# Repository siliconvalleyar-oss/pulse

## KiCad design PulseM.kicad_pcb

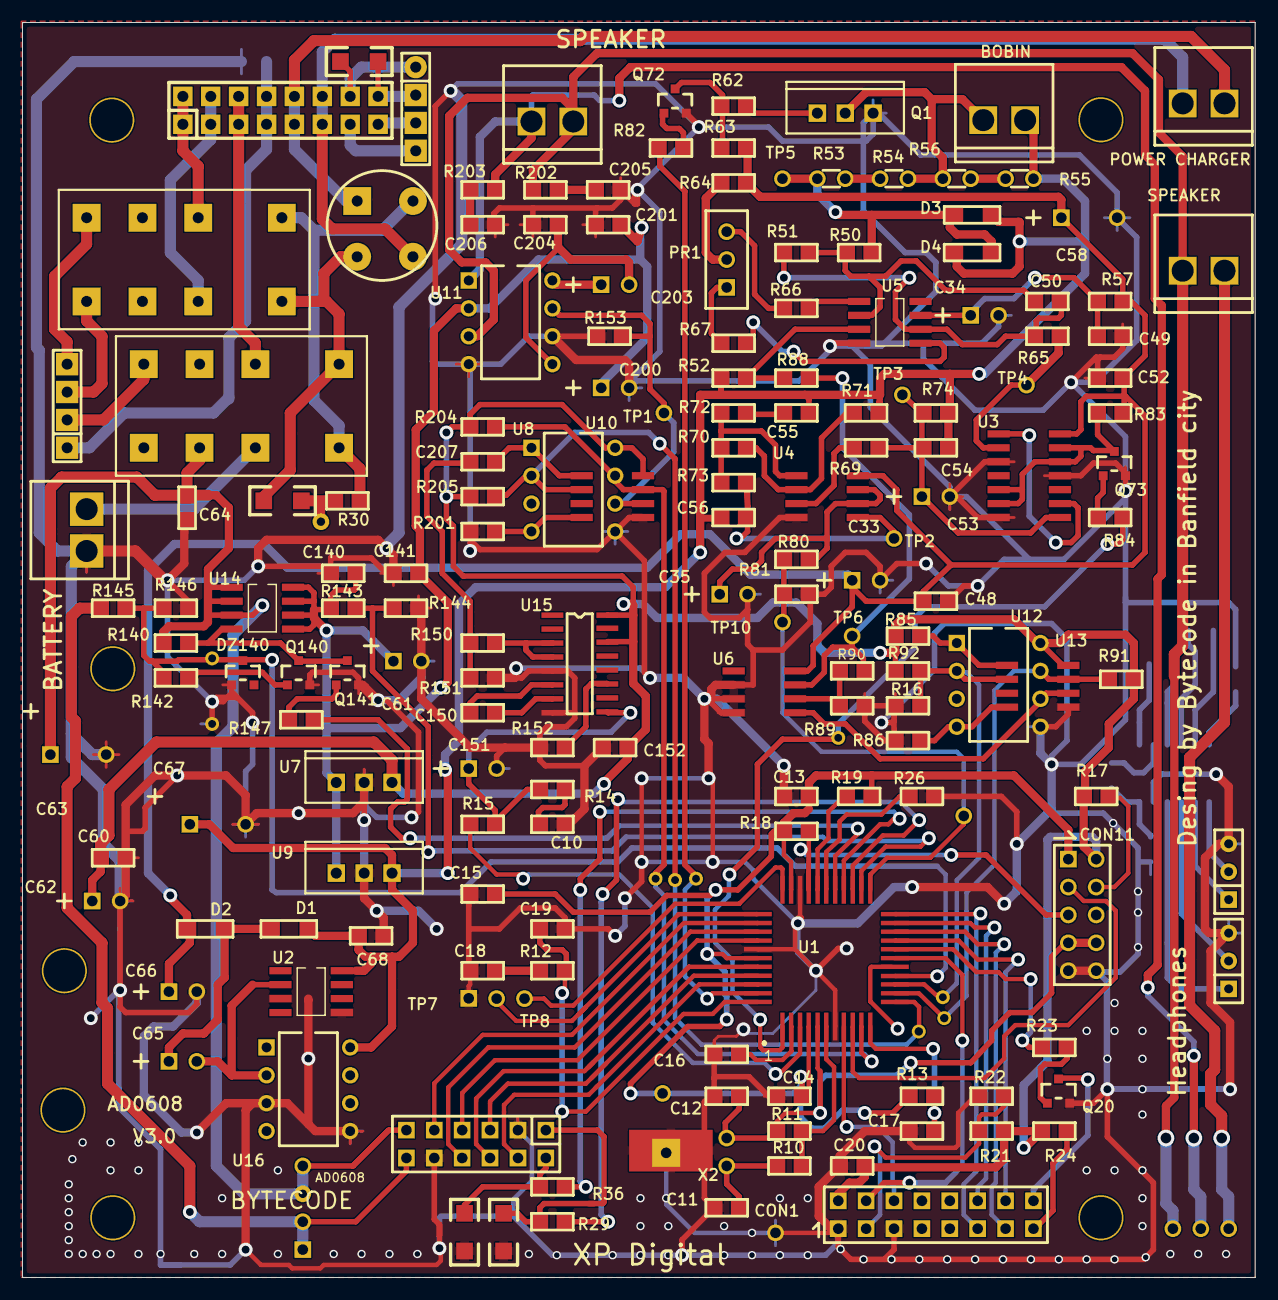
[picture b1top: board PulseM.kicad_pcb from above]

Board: 2 copper layers, 112.3 x 114.3 mm, 205 parts (0 on the bottom side), 136 nets.

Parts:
4Cell: SIP4
BALANCER: IDC16
BATTERY: NEWBOR
BOBIN: NEWBOR
BRIDGE: BRIDGE
Button: CON12SIL
C10, C13, C14, C15, C16, C17, C20, C48, C49, C60#2, C64#2, C68, C141, C152, C201, C204, C205, C206: 100nF; 0805
C11, C12: 27pF; 0805
C18: 470nF; 0805
C19: 22nF; 0805
C33, C61#2, C62#2, C65, C151, C200, C203: 10uF/16V; CAP100RP
C34: 100uF/25V; CAP100RP
C35: 1uF/25V; CAP100RP
C50, C207: 470pF; 0805
C52, C54, C55, C56: 100n; 0805
C53: 1uF/16V; CAP100RP
C58: 1000uF/25V; CAP200RP
C60, C61, C62, C63#2, C64: 0805
C63, C67: 1000uF/25V; CAP200RP2
C66: 47uF/25V; CAP100RP
C140: 1uF; 0805
C150: 10nF; 0805
CON1: DISPLAY LCD; CON16F2
CON11: CON10FF
D1, D2, D3, D4: 1N4148; 1206K
DZ140: 4V7; SOT-23(A1A2K)
FP1, FP2, FP4, FP5, FP6, FP7, FP8, FP9, FP10, FP11, FP12, FP16, FP17, FP18, FP20, FP22, FP23, FP24, FP27, FP28, FP105, FP105#2, FP105#3, FP105#4, FP105#5, FP105#6, FP105#7: FreePad
LED CHARGER: SIP4
Led1, Led2, Led3, Led4: 1206
NR1, NR2, NR3: CAP200RP2
PO1, PO2: SIP3
POWER CHARGER: NEWBOR
PR1: 200K - MULTIVUELTAS; PR3
Q1: TO220
Q20: SOT-23(BEC)
Q72, Q73, Q140, Q141: BC846; SOT-23(BEC)
R10: 330K; 0805
R11, R51: 10M; 0805
R12: 2K2; 0805
R13, R17, R18, R19, R21, R23, R26, R63, R66, R67, R69, R74, R80, R82, R83, R84, R85, R86, R89, R91, R92, R142, R143, R147: 10K; 0805
R14, R201: 0; 0805
R15, R70, R146: 47K; 0805
R16, R64, R72, R73, R88: 100K; 0805
R22, R29, R30, R31, R36, R65, R144: 1K; 0805
R24: 10; 0805
R50, R52, R57: 100; 0805
R53, R55: 390; RES100
R54, R56: 100; RES100
R62: 56; 0805
R71: 330; 0805
R81, R145, R153: 4K7; 0805
R90: 33K; 0805
R140: 100k; 0805
R150: 390k; 0805
R151: 470; 0805
R152: 150k; 0805
R202, R203: 10R; 0805
R204, R205: 10k; 0805
RL1, RL2: RELE
SPEAKER: NEWBOR
SPEAKER#2: NEWBOR
TP1: AUDIO; TP
TP2: AMP2; TP
TP3: SAMP; TP
TP4: AMP1; TP
TP5: PULSE; TP
TP6: AJUSTE; TP
TP7: BT7; TP
TP8: BT8; TP
TP10: ADC; TP
U1: MC68HC908AP32QFP44; QFP44
U2, U4, U5, U6, U10, U13: SO8
U3: SO14
U7: TO220
U8, U12: DIP-8
U9: 7809; TO220
U11, U16: DIP8
U14: IRF7204; SO8
U15: NSOIC16
U50: SO16
X2: 32768Hz; CRYSTAL100

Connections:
5VCC: C13.2, C14.2, C15.2, CON11.1, FP23.23, R13.2, R18.2, R19.1, U1.4, U1.32, U1.39
9V: BOBIN.2, C54.1, C55.1, C56.1, C67.1, C68.1, D1.1, D3.1, D4.2, R52.1, R55.1, R71.1, R74.1, U2.8, U9.3, U16.8
16V: C33.1, C48.1, C52.1, C58.1, C66.1, D2.2, R57.1, R63.1, R64.1, R83.2, U3.14, U4.8, U6.8
+5: C60.2, C64.2, U50.16
+5V: C20.2, C60#2.1, C62#2.1, C152.1, CON1.2, CON11.2, R17.2, R21.1, R24.1, R85.1, R91.2, R92.2, R204.2, R205.2, U7.3, U8.8, U10.8, U12.8, U13.8, U15.14, U15.16
+12V: C61#2.1, C140.2, C141.2, C200.1, C201.2, R143.2, U7.1, U9.1, U11.2, U14.5, U14.6, U14.7, U14.8
ADCMET1: C56.2, R73.1, TP2.1, U4.5
ADCMETAL: FP22.22, R80.2, R81.1, TP10.1, U1.23
ADCMETALHV: C35.1, R80.1, U4.6, U4.7
AJUSTE: R88.1, R90.2, TP6.1, U6.7
AJUSTE5V: U6.5, U12.6, U13.6
AJUSTEINTER: C207.1, U8.1, U10.1
AJUSTENEG: R201.2, U8.4, U10.4
AMP1: R65.2, TP4.1, U3.2
AONIVE: R70.1, R71.2, U4.2
AOOUT: R70.2, R72.2, R73.2, U4.1
AUDIOATENU: R153.1, TP1.1, U8.6, U10.6, U11.7
AUDIO_IN: C151.1, R14.1, R15.1, U15.9
AUDIO_OUT: C207.2, R150.1, R151.1
BACKA: CON1.15, R24.2
BACKBA: Q20.1, R23.1
BACKC: CON1.16, Q20.2
BACKLIGHT: R23.2, U1.18
BOTON1: Button.4, U1.42
BOTON2: Button.5, U1.41
BOTON3: Button.6, U1.40
BOTON4: Button.7, U1.37
BOTON5: Button.8, U1.36
BOTON6: Button.9, U1.35
BOTON7: TP7.1, U1.34
BOTON8: TP8.1, U1.33
C1NET00004: C150.1, U15.6
C1NET00010: C150.2, U15.7
CEL1: 4Cell.1, BALANCER.7, BALANCER.8, R31.1
CEL2: BALANCER.5, BALANCER.6, RL1.2
CEL3: BALANCER.3, BALANCER.4, RL2.7
CHARGE-: FP12.12, SPEAKER.2
CONTLCD: CON1.3, R21.2, R22.1
ENCENDIDO: Q140.2, Q141.2, R140.2, U14.4
ENTREERES: R53.1, R54.2
FILTROIN: C55.2, R72.1
FLITMIC: C18.1, R12.1
GNDA: BATTERY.1, Button.3, Button.10, C10.1, C11.2, C12.2, C13.1, C14.1, C15.1, C16.1, C17.2, C18.2, C19.2, C20.1, C33.2, C34.2, C35.2, C48.2, C49.2, C52.2, C53.2, C58.2, C60#2.2, C61#2.2, C62#2.2, C63.2, C63#2.2, C64.1, C64#2.2, C66.2, C67.2, C68.2, C140.1, C141.1, C151.2, C152.2, C200.2, C201.1, C204.1, C205.1, C206.1, CON1.1, CON1.5, CON11.9, CON11.10, DZ140.1, FP1.1, FP17.17, FP27.27, Led1.2, Led2.2, NR1.1, NR3.1, PO1.3, PO2.3, Q1.3, Q20.3, Q72.3, Q73.3, Q140.3, Q141.3, R16.1, R22.2, R26.1, R31.2, R81.2, R86.2, R89.1, R144.1, R146.1, R151.2, R152.1, R153.2, R201.1, U1.7, U1.31, U1.38, U2.3, U2.5, U3.3, U3.7, U3.11, U4.4, U5.4, U6.2, U6.3, U6.4, U7.2, U8.5, U9.2, U10.5, U11.4, U11.6, U12.5, U13.5, U15.5, U15.8, U16.3, U16.5, U50.15
INAUDFIOD: C203.2, C204.2, U11.5
IRQ: CON11.4, R17.1
IRQINT: CON11.3, U1.9
KEWPWRBASE: Q140.1, R142.1
KEY_SENSE: DZ140.3, FP16.16, R142.2, R145.2, R146.2, U1.15
LCDDATA1: CON1.11, U1.22
LCDDATA2: CON1.12, U1.21
LCDDATA3: CON1.13, U1.20
LCDDATA4: CON1.14, U1.19
LCDE: CON1.6, U1.8
LCDRS: CON1.4, U1.17
LED1: R29.1, U1.25
LED2: R36.1, U1.26
LLAVEDISP: Q73.2, R83.1, U3.5, U3.6, U3.12, U3.13
LLAVEINTER: U3.1, U3.9
LLAVEPOUT: C53.1, C54.2, R69.1, R74.2, TP3.1, U3.8
LMSALIDA1: C50.2, R51.2, R65.1, U5.6
MEDIR_VCC: R143.1, R144.2, U1.24
N4V7: FP4.4, Led3.2, R30.2
NET00000: R66.2, U5.1
NET00001: R67.2, U5.5
NET00002: Button.1, Led1.1, R29.2
NET00003: Button.2, Led2.1, R36.2
NET00008: C205.2, R202.1
NET00011: C206.2, R203.1
NET00012: C203.1, U11.8
NET00022: C34.1, C49.1, R57.2, U5.7
NET00035: C10.2, R14.2
NET00046: R26.2, U1.28
NET00052: R19.2, U1.29
NET00069: R89.2, R90.1, U6.6
NET00070: R85.2, U12.1, U13.1
NET00071: R86.1, U12.4, U13.4
NET00102: C65.1, D1.2, D2.1
NET00103: C65.2, U2.2, U16.2
NET00107: R52.2, R88.2, U5.3
NET00110: BOBIN.1, Q1.2, R54.1, R56.2
NET00111: R55.2, R56.1
NET00112: Q1.1, R62.1
NET00113: Q72.2, R62.2, R63.2
NET00114: Q72.1, R82.1
NET00115: PR1.1, R67.1
NET00116: PR1.3, R66.1
NET00117: PR1.2, R64.2
NET00124: Q73.1, R84.1
NET00128: R69.2, U4.3
NET00132: R10.2, R11.1, U1.6
NET00134: C19.1, R12.2, U1.44
NET00144: C11.1, R10.1, X2.1
NET00160: C16.2, U1.2
NetC61_1: C61.1, U50.1
NetC61_2: C61.2, U50.3
NetC62_1: C62.1, U50.4
NetC62_2: C62.2, U50.5
NetC63_1: C63#2.1, U50.6
NetLED_1: BALANCER.14, LED CHARGER.1, Led4.1
NetLED_2: BALANCER.16, LED CHARGER.2, Led4.2
NetLED_3: BALANCER.15, LED CHARGER.3
NetLED_4: BALANCER.13, LED CHARGER.4
NetRL1_4: 4Cell.2, RL1.4
NetRL1_5: BATTERY.2, RL1.7
NetRL2_4: 4Cell.4, RL2.4
NetRL2_5: 4Cell.3, RL2.5
NetU50_2: C60.1, U50.2
NetU50_11: PO1.2, U50.11
NetU50_12: PO1.1, U50.12
NetU50_13: PO2.2, U50.13
NetU50_14: PO2.1, U50.14
OPEINTE: C50.1, R50.2, R51.1, U5.2
OSC1: C12.1, CON11.7, CON11.8, R11.2, U1.5, X2.2
PORTA0: CON11.5, R18.1, U1.30
PULSEAMPL: D3.2, D4.1, R50.1, R53.2, TP5.1
PULSO: FP7.7, R82.2, U1.43
PWR1: Button.11, C63.1, C64#2.1, FP2.2, FP18.18, R140.1, RL1.6, U14.1, U14.2, U14.3
PWR2: Button.12, FP20.20, NR2.1, R145.1
RESETM: C17.1, R13.1, U1.11
RETENCION_POWER: R147.1, U1.27
RETPOW1: Q141.1, R147.2
RVCO: R152.2, U15.11
SAMPLE: FP28.28, R84.2, U1.1
SENS+: FP24.24, R16.2, R92.1, U1.14, U12.2, U13.2
SENS-: FP8.8, R91.1, U1.13, U12.7, U13.7
SPKR_N: FP10.10, R202.2, SPEAKER.1, SPEAKER#2.2, U11.3
SPKR_P: FP11.11, R203.2, SPEAKER#2.1, U11.1
TIMEROUT: R15.2, U1.3
V1: BALANCER.9, BALANCER.10, BRIDGE.1, POWER CHARGER.2
V2: BALANCER.11, BALANCER.12, BRIDGE.3, POWER CHARGER.1
V+: BRIDGE.2, R30.1, RL1.8, RL2.1
V-: BRIDGE.4, Led3.1, RL1.1, RL2.8
VCO_OUT: R150.2, U15.3, U15.4
VOL+: FP6.6, FP9.9, R205.1, U1.12, U8.2, U10.2
VOL-: FP5.5, R204.1, U1.10, U8.7, U10.7
VSS: BALANCER.1, BALANCER.2, RL2.2

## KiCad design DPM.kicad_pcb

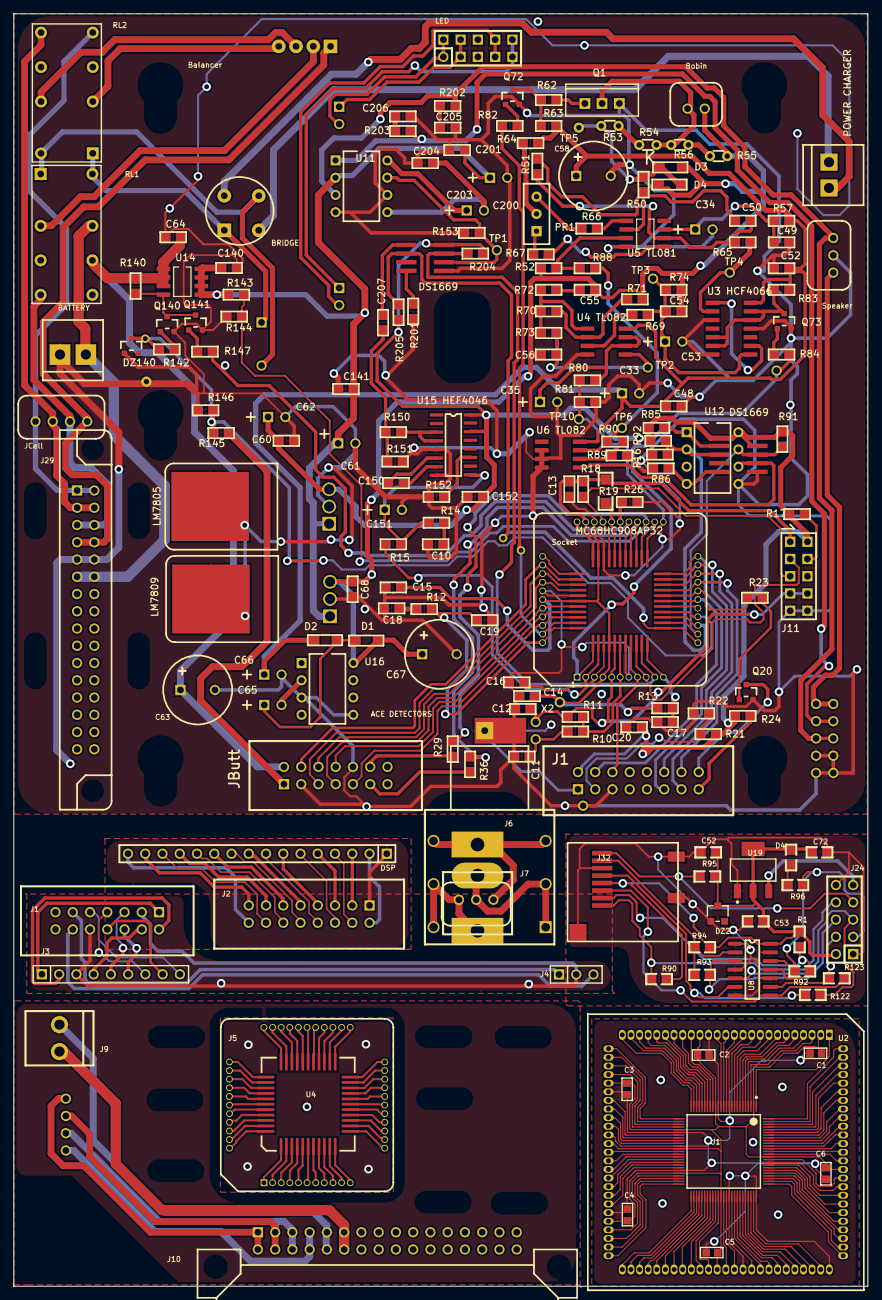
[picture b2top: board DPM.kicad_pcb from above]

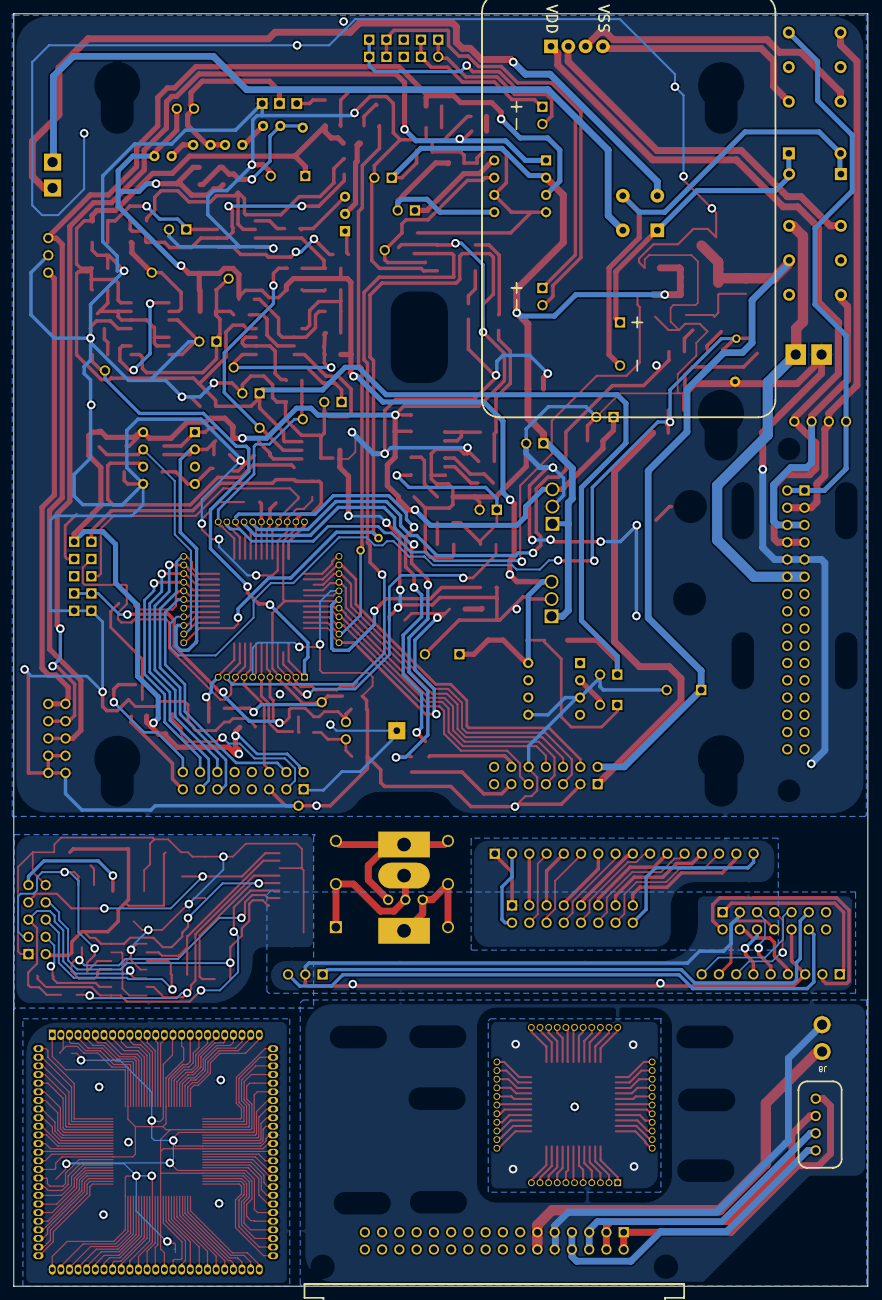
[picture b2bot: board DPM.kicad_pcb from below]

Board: 2 copper layers, 125.7 x 187.3 mm, 197 parts (38 on the bottom side), 307 nets.

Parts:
BATTERY: NEWBOR
BRIDGE: BRIDGE
Balancer: Comment; BALANCER 18V
Bobin: SIP2PST7600
C1, C2, C3, C4, C5, C6: 100n; 0603
C10, C13, C14, C15, C16, C17, C20, C48, C49, C60, C64, C68, C141, C152, C201, C204, C205, C206: 100nF; 0805
C11, C12: 27pF; 0805
C18: 470nF; 0805
C19: 22nF; 0805
C33, C61, C62, C65, C151, C200, C203: 10uF/16V; CAP100RP
C34: 100uF/25V; CAP100RP
C35: 1uF/25V; CAP100RP
C50, C207: 470pF; 0805
C52, C52#2, C54, C55, C56, C72: 100n; 0805
C53: 1uF/16V; CAP100RP
C53#2: 1u; 0805
C58: Comment; C200+
C63: 1000; C200+
C66: 47uF/25V; CAP100RP
C67: 1000uF/25V; C200+
C140: 1uF; 0805
C150: 10nF; 0805
D1, D2, D3, D4: 1N4148; 1206K
D4#2: D; 0805
DS1669, DS1669#2: SO8
DSP: SIP16
DZ2: BZX84C3V3LT1; SOT23
DZ140: 4V7; SOT-23(A1A2K)
Designator27: Comment; JACK 63
J1, J2: IDC16X
J1#2: IDC14X
J3: SIP9
J4: SIP3
J5: TQFP44; S127TQFP44
J6: SPK
J7: SIP3PST7600
J8: SIP4PST7600
J9: HEADER2
J10: IDC; DIN41612F
J11: CON10FF
J24: IDC10
J29: Comment; DIN41612M
J32: MICROSD
JButt: Comment; IDC14X
JCell: Comment; SIP4PST7600
LED: Comment; IDC10
LM7805: TO220H
LM7809: 7809; TO220H
MC68HC908AP32: MC68HC908AP32QFP44; QFP44
POWER CHARGER: NEWBOR
PR1: 200K - MULTIVUELTAS; PR3
Q1: TO220
Q20: SOT-23(BEC)
Q72, Q73, Q140, Q141: BC846; SOT-23(BEC)
R1, R13, R17, R18, R21, R23, R26, R63, R66, R67, R69, R74, R80, R82, R83, R84, R85, R86, R89, R90#2, R91, R92, R92#2, R93, R94, R95, R96, R122, R123, R142, R143, R147: 10K; 0805
R10: 330K; 0805
R11, R51: 10M; 0805
R12: 2K2; 0805
R14, R201: 0; 0805
R15, R70, R146: 47K; 0805
R16, R64, R72, R73, R88: 100K; 0805
R19: 10K; 1206
R22, R29, R36, R65, R144: 1K; 0805
R24: 10; 0805
R50, R52, R57: 100; 0805
R53, R55: 390; RES100
R54, R56: 100; RES100
R62: 56; 0805
R71: 330; 0805
R81, R145, R153: 4K7; 0805
R90: 33K; 0805
R140: 100k; 0805
R150: 390k; 0805
R151: 470; 0805
R152: 150k; 0805
R202, R203: 10R; 0805
R204, R205: 10k; 0805
RL1, RL2: RELE
Socket: S127TQFP44
Speaker: Comment; SIP3PST7600
TP1: AUDIO; TP
TP2: AMP2; TP
TP3: SAMP; TP
TP4: AMP1; TP
TP5: PULSE; TP
TP6: AJUSTE; TP
TP10: ADC; TP
U1: PIC32; TQFP12X12-G100/N PT
U2: PIC24FJ; MA240011
U3 HCF4066: SO14
U4: TQFP44; QFP44
U4 TL082, U5 TL081, U6 TL082: SO8
U8: 74HC125; SOIC14
U11, U16: DIP8
U12: DIP-8
U14: IRF7204; SO8
U15 HEF4046: NSOIC16
U19: L1117; SOT223
X2: 32768Hz; CRYSTAL100

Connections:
5VCC: C13.2, C14.2, C15.2, J11.1, MC68HC908AP32.4, MC68HC908AP32.32, MC68HC908AP32.39, R13.2, R18.2, R19.1, Socket.4, Socket.32, Socket.39
9V: Bobin.2, C54.1, C55.1, C56.1, C67.1, C68.1, D1.1, D3.1, D4.2, LM7809.3, R52.1, R55.1, R71.1, R74.1, U16.8
16V: C33.1, C48.1, C52.1, C58.1, C66.1, D2.2, R57.1, R63.1, R64.1, R83.2, U3 HCF4066.14, U4 TL082.8, U6 TL082.8
+3V3: C1.1, C2.1, C3.1, C4.1, C5.1, C6.1, U1.2, U1.16, U1.30, U1.37, U1.46, U1.62, U1.86, U2.2, U2.16, U2.30, U2.37, U2.46, U2.62, U2.86
+5V: C20.2, C60.1, C62.1, C152.1, DS1669.8, DS1669#2.8, J1.2, J11.2, LM7805.3, R17.2, R21.1, R24.1, R85.1, R91.2, R92.2, R204.2, R205.2, U12.8, U15 HEF4046.14, U15 HEF4046.16
+12V: C61.1, C140.2, C141.2, C200.1, C201.2, LM7805.1, LM7809.1, R143.2, U11.2, U14.5, U14.6, U14.7, U14.8
ADCMET1: C56.2, R73.1, TP2.1, U4 TL082.5
ADCMETAL: MC68HC908AP32.23, R80.2, R81.1, Socket.23, TP10.1
ADCMETALHV: C35.1, R80.1, U4 TL082.6, U4 TL082.7
AJUSTE: R88.1, R90.2, TP6.1, U6 TL082.7
AJUSTE5V: DS1669#2.6, U6 TL082.5, U12.6
AJUSTEINTER: C207.1, DS1669.1
AJUSTENEG: DS1669.4, R201.2
AMP1: R65.2, TP4.1, U3 HCF4066.2
AONIVE: R70.1, R71.2, U4 TL082.2
AOOUT: R70.2, R72.2, R73.2, U4 TL082.1
AUDIOATENU: DS1669.6, R153.1, TP1.1, U11.7
AUDIO_IN: C151.1, R14.1, R15.1, U15 HEF4046.9
AUDIO_OUT: C207.2, R150.1, R151.1
BACKA: J1.15, R24.2
BACKBA: Q20.1, R23.1
BACKC: J1.16, Q20.2
BACKLIGHT: MC68HC908AP32.18, R23.2, Socket.18
BOTON1: JButt.9, MC68HC908AP32.42, Socket.42
BOTON2: JButt.8, MC68HC908AP32.41, Socket.41
BOTON3: JButt.7, MC68HC908AP32.40, Socket.40
BOTON4: JButt.6, MC68HC908AP32.37, Socket.37
BOTON5: JButt.5, MC68HC908AP32.36, Socket.36
BOTON6: JButt.4, MC68HC908AP32.35, Socket.35
BOTON7: MC68HC908AP32.34, Socket.34
BOTON8: MC68HC908AP32.33, Socket.33
C1NET00004: C150.1, U15 HEF4046.6
C1NET00010: C150.2, U15 HEF4046.7
CEL1: Balancer.7, RL2.2
CEL2: Balancer.8, RL2.7
CEL3: Balancer.9, RL1.2
CONTLCD: J1.3, R21.2, R22.1
CS: J24.3, R92#2.2, R96.1, U8.12
CS_: J32.2, R1.1, R92#2.1, U8.11
DAT1: J24.7, J32.8, R95.1
DAT2: J24.8, J32.1, R90#2.1
ENCENDIDO: Q140.2, Q141.2, R140.2, U14.4
ENTREERES: R53.1, R54.2
FILTROIN: C55.2, R72.1
FLITMIC: C18.1, R12.1
GND: C1.2, C2.2, C3.2, C4.2, C5.2, C6.2, U1.15, U1.31, U1.36, U1.45, U1.65, U1.75, U2.15, U2.31, U2.36, U2.45, U2.65, U2.75
GND2: J1#2.3, J1#2.10, J3.3, J4.2
GNDA: BATTERY.1, C10.1, C11.2, C12.2, C13.1, C14.1, C15.1, C16.1, C17.2, C18.2, C19.2, C20.1, C33.2, C34.2, C35.2, C48.2, C49.2, C52.2, C53.2, C58.2, C60.2, C61.2, C62.2, C63.2, C64.2, C66.2, C67.2, C68.2, C140.1, C141.1, C151.2, C152.2, C200.2, C201.1, C204.1, C205.1, C206.1, DS1669.5, DS1669#2.5, DZ140.1, J1.1, J1.5, J11.9, J11.10, J29.9, J29.10, JButt.3, JButt.10, LM7805.2, LM7809.2, MC68HC908AP32.7, MC68HC908AP32.31, MC68HC908AP32.38, Q1.3, Q20.3, Q72.3, Q73.3, Q140.3, Q141.3, R16.1, R22.2, R26.1, R81.2, R86.2, R89.1, R144.1, R146.1, R151.2, R152.1, R153.2, R201.1, Socket.7, Socket.31, Socket.38, Speaker.2, U3 HCF4066.3, U3 HCF4066.7, U3 HCF4066.11, U4 TL082.4, U5 TL081.4, U6 TL082.2, U6 TL082.3, U6 TL082.4, U11.4, U11.6, U12.5, U15 HEF4046.5, U15 HEF4046.8, U16.3, U16.5
INAUDFIOD: C203.2, C204.2, U11.5
IRQ: J11.4, R17.1
IRQINT: J11.3, MC68HC908AP32.9, Socket.9
KEWPWRBASE: Q140.1, R142.1
KEY_SENSE: DZ140.3, MC68HC908AP32.15, R142.2, R145.2, R146.2, Socket.15
LCDDATA1: J1.11, MC68HC908AP32.22, Socket.22
LCDDATA2: J1.12, MC68HC908AP32.21, Socket.21
LCDDATA3: J1.13, MC68HC908AP32.20, Socket.20
LCDDATA4: J1.14, MC68HC908AP32.19, Socket.19
LCDE: J1.6, MC68HC908AP32.8, Socket.8
LCDRS: J1.4, MC68HC908AP32.17, Socket.17
LED1: MC68HC908AP32.25, R29.1, Socket.25
LED2: MC68HC908AP32.26, R36.1, Socket.26
LLAVEDISP: Q73.2, R83.1, U3 HCF4066.5, U3 HCF4066.6, U3 HCF4066.12, U3 HCF4066.13
LLAVEINTER: U3 HCF4066.1, U3 HCF4066.9
LLAVEPOUT: C53.1, C54.2, R69.1, R74.2, TP3.1, U3 HCF4066.8
LM317ADJ: MC68HC908AP32.16, Socket.16
LMSALIDA1: C50.2, R51.2, R65.1, U5 TL081.6
MEDIR_VCC: MC68HC908AP32.24, R143.1, R144.2, Socket.24
NET00000: R66.2, U5 TL081.1
NET00001: R67.2, U5 TL081.5
NET00002: JButt.12, R29.2
NET00003: JButt.11, R36.2
NET00008: C205.2, R202.1
NET00011: C206.2, R203.1
NET00012: C203.1, U11.8
NET00022: C34.1, C49.1, R57.2, U5 TL081.7
NET00035: C10.2, R14.2
NET00046: MC68HC908AP32.28, R26.2, Socket.28
NET00052: MC68HC908AP32.29, R19.2, Socket.29
NET00069: R89.2, R90.1, U6 TL082.6
NET00070: DS1669#2.1, R85.2, U12.1
NET00071: DS1669#2.4, R86.1, U12.4
NET00102: C65.1, D1.2, D2.1
NET00103: C65.2, U16.2
NET00107: R52.2, R88.2, U5 TL081.3
NET00110: Bobin.1, Q1.2, R54.1, R56.2
NET00111: R55.2, R56.1
NET00112: Q1.1, R62.1
NET00113: Q72.2, R62.2, R63.2
NET00114: Q72.1, R82.1
NET00115: PR1.1, R67.1
NET00116: PR1.3, R66.1
NET00117: PR1.2, R64.2
NET00124: Q73.1, R84.1
NET00128: R69.2, U4 TL082.3
NET00132: MC68HC908AP32.6, R10.2, R11.1, Socket.6
NET00134: C19.1, MC68HC908AP32.44, R12.2, Socket.44
NET00144: C11.1, R10.1, X2.1
NET00160: C16.2, MC68HC908AP32.2, Socket.2
NETA: DSP.1, J2.1
NETB: DSP.2, J2.2
NETC: DSP.3, J2.3
NETD: DSP.4, J2.4
NETE: DSP.5, J2.5
NETF: DSP.6, J2.6
NETG: DSP.7, J2.7
NETH: DSP.8, J2.8
NETI: DSP.9, J2.9
NETJ: DSP.10, J2.10
NETK: DSP.11, J2.11
NETL: DSP.12, J2.12
NETM: DSP.13, J2.13
NETN: DSP.14, J2.14
NETO: DSP.15, J2.15
NETP: DSP.16, J2.16
NetD4_2: D4#2.2, R96.2
NetJ1_1: J1#2.1, J3.1
NetJ1_2: J1#2.2, J3.2
NetJ1_4: J1#2.4, J3.4
NetJ1_5: J1#2.5, J3.5
NetJ1_6: J1#2.6, J3.6
NetJ1_7: J1#2.7, J3.7
NetJ1_8: J1#2.8, J3.8
NetJ1_9: J1#2.9, J3.9
NetJ1_11: J1#2.11, J4.1
NetJ1_12: J1#2.12, J4.3
NetJ5_1: J5.1, U4.1
NetJ5_2: J5.2, U4.2
NetJ5_3: J5.3, U4.3
NetJ5_4: J5.4, U4.4
NetJ5_5: J5.5, U4.5
NetJ5_6: J5.6, U4.6
NetJ5_7: J5.7, U4.7
NetJ5_8: J5.8, U4.8
NetJ5_9: J5.9, U4.9
NetJ5_10: J5.10, U4.10
NetJ5_11: J5.11, U4.11
NetJ5_12: J5.12, U4.12
NetJ5_13: J5.13, U4.13
NetJ5_14: J5.14, U4.14
NetJ5_15: J5.15, U4.15
NetJ5_16: J5.16, U4.16
NetJ5_17: J5.17, U4.17
NetJ5_18: J5.18, U4.18
NetJ5_19: J5.19, U4.19
NetJ5_20: J5.20, U4.20
NetJ5_21: J5.21, U4.21
NetJ5_22: J5.22, U4.22
NetJ5_23: J5.23, U4.23
NetJ5_24: J5.24, U4.24
NetJ5_25: J5.25, U4.25
NetJ5_26: J5.26, U4.26
NetJ5_27: J5.27, U4.27
NetJ5_28: J5.28, U4.28
NetJ5_29: J5.29, U4.29
NetJ5_30: J5.30, U4.30
NetJ5_31: J5.31, U4.31
NetJ5_32: J5.32, U4.32
NetJ5_33: J5.33, U4.33
NetJ5_34: J5.34, U4.34
NetJ5_35: J5.35, U4.35
NetJ5_36: J5.36, U4.36
NetJ5_37: J5.37, U4.37
NetJ5_38: J5.38, U4.38
NetJ5_39: J5.39, U4.39
NetJ5_40: J5.40, U4.40
NetJ5_41: J5.41, U4.41
NetJ5_42: J5.42, U4.42
NetJ5_43: J5.43, U4.43
NetJ5_44: J5.44, U4.44
NetJ6_1: Designator27.2, Designator27.4, J6.1, J7.3
NetJ6_2: Designator27.1, Designator27.3, J6.2, J7.2
NetJ6_3: Designator27.5, Designator27.6, J6.3, J7.1
NetJ8_1: J8.1, J10.1, J10.2
NetJ8_2: J8.2, J10.3, J10.4
NetJ8_3: J8.3, J10.5, J10.6
NetJ8_4: J8.4, J10.7, J10.8
NetJ9_1: J9.1, J10.9, J10.10
NetJ9_2: J9.2, J10.11, J10.12
NetLED_1: Balancer.4, LED.9, LED.10
NetLED_2: Balancer.3, LED.7, LED.8
NetLED_3: Balancer.6, LED.3, LED.4
NetLED_4: Balancer.5, LED.1, LED.2
NetRL1_4: J29.5, J29.6, JCell.3, RL1.4
NetRL1_5: BATTERY.2, J29.11, J29.12, RL1.7
NetRL2_4: J29.1, J29.2, JCell.1, RL2.4
NetRL2_5: J29.3, J29.4, JCell.2, RL2.5
NetU1_1: U1.1, U2.1
NetU1_3: U1.3, U2.3
NetU1_4: U1.4, U2.4
NetU1_5: U1.5, U2.5
NetU1_6: U1.6, U2.6
NetU1_7: U1.7, U2.7
NetU1_8: U1.8, U2.8
NetU1_9: U1.9, U2.9
NetU1_10: U1.10, U2.10
NetU1_11: U1.11, U2.11
NetU1_12: U1.12, U2.12
NetU1_13: U1.13, U2.13
NetU1_14: U1.14, U2.14
NetU1_17: U1.17, U2.17
NetU1_18: U1.18, U2.18
NetU1_19: U1.19, U2.19
NetU1_20: U1.20, U2.20
NetU1_21: U1.21, U2.21
NetU1_22: U1.22, U2.22
NetU1_23: U1.23, U2.23
NetU1_24: U1.24, U2.24
NetU1_25: U1.25, U2.25
NetU1_26: U1.26, U2.26
NetU1_27: U1.27, U2.27
NetU1_28: U1.28, U2.28
NetU1_29: U1.29, U2.29
NetU1_32: U1.32, U2.32
NetU1_33: U1.33, U2.33
NetU1_34: U1.34, U2.34
NetU1_35: U1.35, U2.35
NetU1_38: U1.38, U2.38
NetU1_39: U1.39, U2.39
NetU1_40: U1.40, U2.40
NetU1_41: U1.41, U2.41
NetU1_42: U1.42, U2.42
NetU1_43: U1.43, U2.43
NetU1_44: U1.44, U2.44
NetU1_47: U1.47, U2.47
NetU1_48: U1.48, U2.48
NetU1_49: U1.49, U2.49
NetU1_50: U1.50, U2.50
NetU1_51: U1.51, U2.51
NetU1_52: U1.52, U2.52
NetU1_53: U1.53, U2.53
NetU1_54: U1.54, U2.54
NetU1_55: U1.55, U2.55
NetU1_56: U1.56, U2.56
NetU1_57: U1.57, U2.57
NetU1_58: U1.58, U2.58
NetU1_59: U1.59, U2.59
NetU1_60: U1.60, U2.60
NetU1_61: U1.61, U2.61
NetU1_63: U1.63, U2.63
NetU1_64: U1.64, U2.64
NetU1_66: U1.66, U2.66
NetU1_67: U1.67, U2.67
NetU1_68: U1.68, U2.68
NetU1_69: U1.69, U2.69
NetU1_70: U1.70, U2.70
NetU1_71: U1.71, U2.71
NetU1_72: U1.72, U2.72
NetU1_73: U1.73, U2.73
NetU1_74: U1.74, U2.74
NetU1_76: U1.76, U2.76
NetU1_77: U1.77, U2.77
NetU1_78: U1.78, U2.78
NetU1_79: U1.79, U2.79
NetU1_80: U1.80, U2.80
NetU1_81: U1.81, U2.81
NetU1_82: U1.82, U2.82
NetU1_83: U1.83, U2.83
NetU1_84: U1.84, U2.84
NetU1_85: U1.85, U2.85
NetU1_87: U1.87, U2.87
NetU1_88: U1.88, U2.88
NetU1_89: U1.89, U2.89
NetU1_90: U1.90, U2.90
NetU1_91: U1.91, U2.91
NetU1_92: U1.92, U2.92
NetU1_93: U1.93, U2.93
NetU1_94: U1.94, U2.94
NetU1_95: U1.95, U2.95
NetU1_96: U1.96, U2.96
NetU1_97: U1.97, U2.97
NetU1_98: U1.98, U2.98
NetU1_99: U1.99, U2.99
NetU1_100: U1.100, U2.100
OPEINTE: C50.1, R50.2, R51.1, U5 TL081.2
OSC1: C12.1, J11.7, J11.8, MC68HC908AP32.5, R11.2, Socket.5, X2.2
PORTA0: J11.5, MC68HC908AP32.30, R18.1, Socket.30
PULSEAMPL: D3.2, D4.1, R50.1, R53.2, TP5.1
PULSO: MC68HC908AP32.43, R82.2, Socket.43
PWR1: C63.1, C64.1, JButt.2, R140.1, RL1.6, U14.1, U14.2, U14.3
PWR2: JButt.1, R145.1
RESETM: C17.1, MC68HC908AP32.11, R13.1, Socket.11
RETENCION_POWER: MC68HC908AP32.27, R147.1, Socket.27
RETPOW1: Q141.1, R147.2
RVCO: R152.2, U15 HEF4046.11
SAMPLE: MC68HC908AP32.1, R84.2, Socket.1
SCK: J24.5, R122.2, U8.5
SCK_: J32.5, R122.1, U8.6
SDI: J24.6, R93.2, U8.3
SDI_: J32.7, R93.1, R94.1, U8.2
SDO: J24.4, R123.2, U8.9
SDO_: J32.3, R123.1, U8.8
SD_GND: C52#2.2, C53#2.2, C72.2, DZ2.1, J24.1, J24.10, J32.6, J32.9, U8.1, U8.4, U8.7, U8.10, U8.13, U19.1
SENS+: DS1669#2.2, MC68HC908AP32.14, R16.2, R92.1, Socket.14, U12.2
SENS-: DS1669#2.7, MC68HC908AP32.13, R91.1, Socket.13, U12.7
SPKR_N: R202.2, Speaker.3, U11.3
SPKR_P: R203.2, U11.1
TIMEROUT: MC68HC908AP32.3, R15.2, Socket.3
USD_+3.3: C52#2.1, C53#2.1, C72.1, D4#2.1, DZ2.3, J24.2, J32.4, R1.2, R90#2.2, R94.2, R95.2, U8.14, U19.2
USD_+5: J24.9, U19.3
V1: BRIDGE.1, POWER CHARGER.2
V2: BRIDGE.3, POWER CHARGER.1
V+: BRIDGE.4, Balancer.2, RL1.8, RL2.1
V-: BRIDGE.2, Balancer.1, RL1.1, RL2.8
VCO_OUT: R150.2, U15 HEF4046.3, U15 HEF4046.4
VOL+: DS1669.2, MC68HC908AP32.12, R205.1, Socket.12
VOL-: DS1669.7, MC68HC908AP32.10, R204.1, Socket.10
VSS: Balancer.10, J29.7, J29.8, JCell.4
